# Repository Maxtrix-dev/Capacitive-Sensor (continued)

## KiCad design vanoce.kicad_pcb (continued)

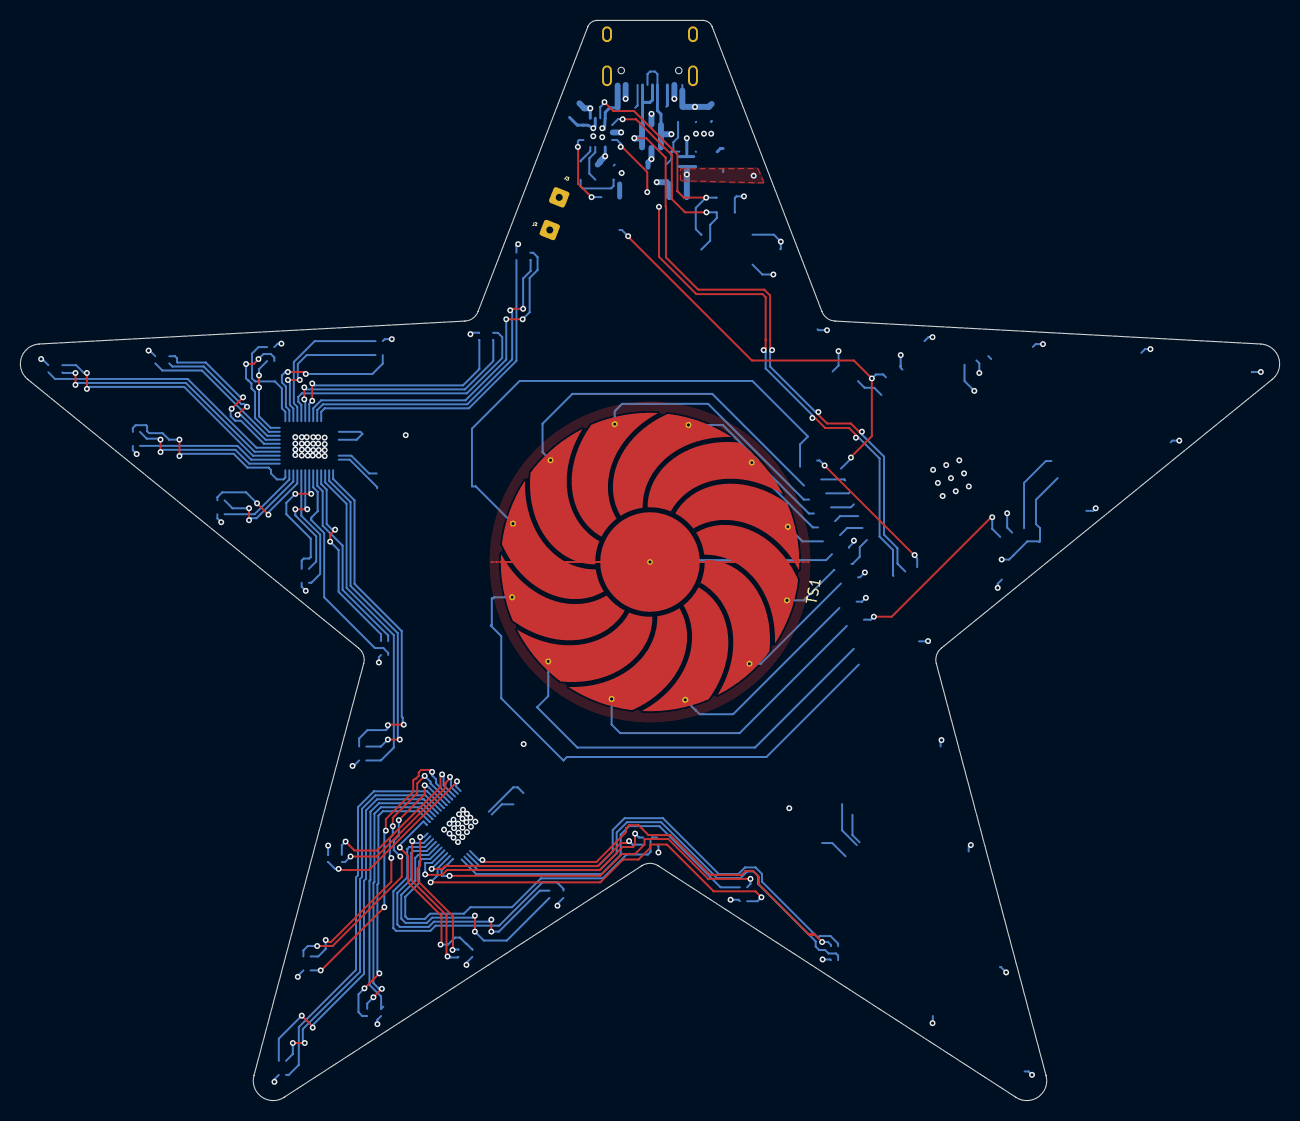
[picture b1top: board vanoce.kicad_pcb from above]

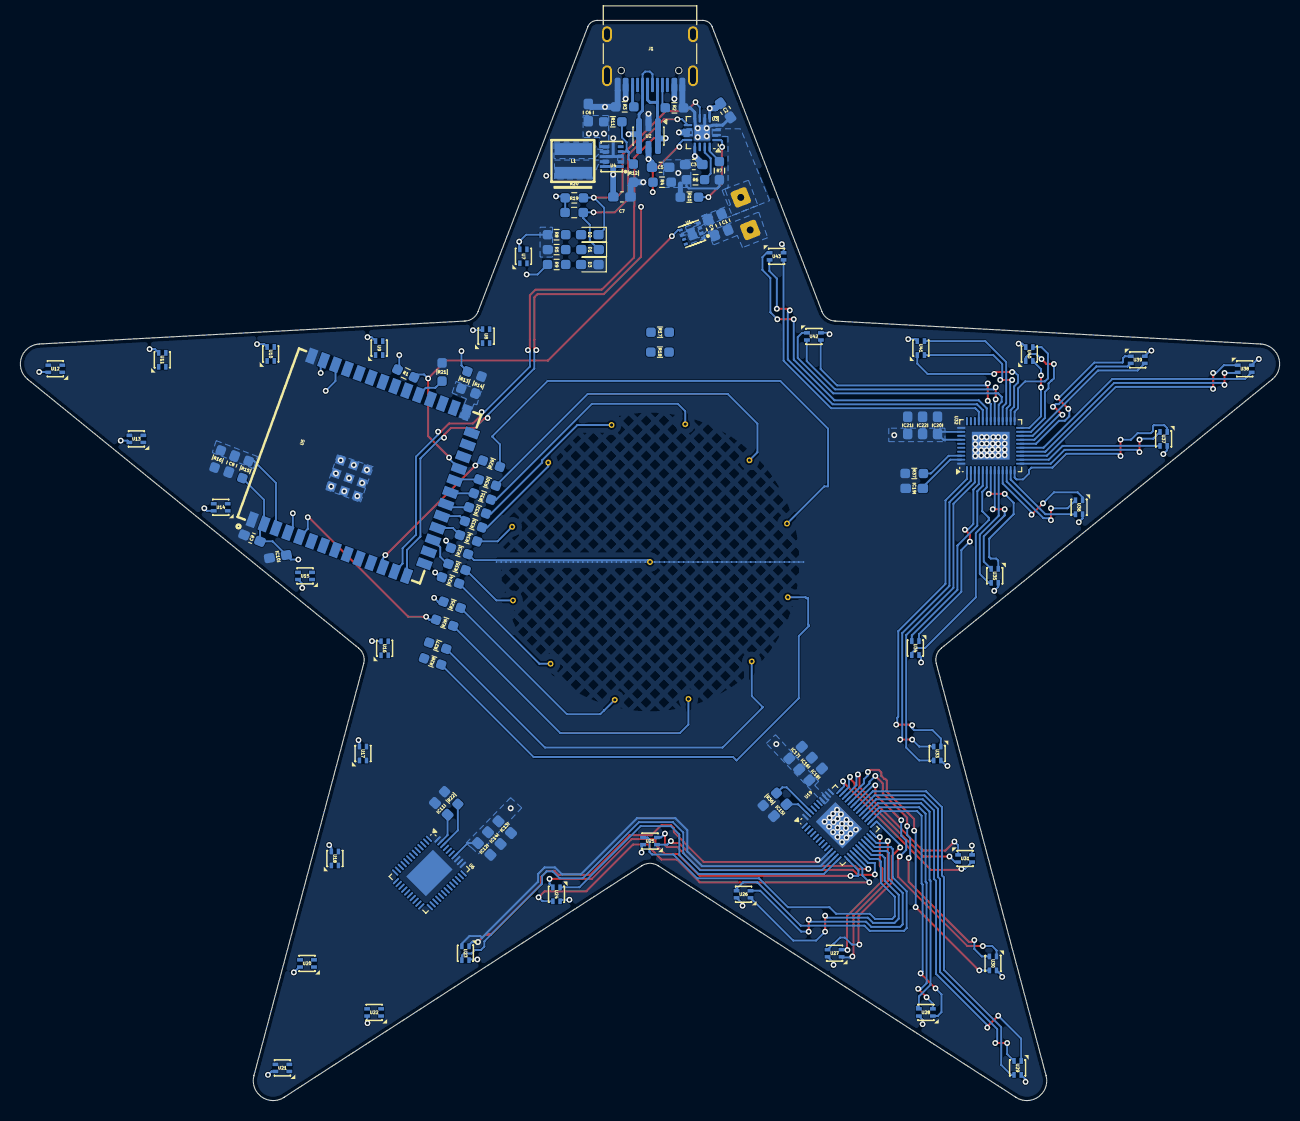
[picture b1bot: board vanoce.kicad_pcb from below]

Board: 4 copper layers, 126.6 x 108.6 mm, 110 parts (107 on the bottom side), 164 nets.

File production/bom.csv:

Designator,Footprint,Quantity,Value,LCSC Part #
"C1, C2",0603,2,4u7,
"C10_2, C10, C13, C17, C21, C5",0603,6,100n,
"C11, C12, C15, C16, C19, C20, C3, C8",0603,8,1u,
"C14, C18, C22, C7",0603,4,10u,
C4,0603,1,0.1u,
"C6, C9",0603,2,22u,
D1,0603,1,GREEN,
D2,0603,1,ORANGE,
D3,0603,1,BLUE,
J1,USB_C_Receptacle_HRO_TYPE-C-31-M-12,1,USB_C_Receptacle_USB2.0_16P,
"J2, J3",SolderWire-0.15sqmm_1x01_D0.5mm_OD1.5mm,2,Conn_01x01_Pin,
L1,IND-SMD_L4.0-W4.0_XFL4020-102MEB,1,XFL4015-471MEC,C18221164
"R1, R19, R20, R21",0603,4,100k,
"R10, R13, R15",0603,3,10k,
R11,0603,1,510k,
R12,0603,1,91k,
"R14, R16",0603,2,DNP,
"R17, R18",0603,2,4k7,
"R2, R3",0603,2,5k1,
"R22, R36, R37",0603,3,6k2,
"R23, R24, R25, R26, R27, R28, R29, R30, R31, R32, R33, R34, R35",0603,13,510R,
R4,0603,1,1k1,
R5,0603,1,6k,
R6,0603,1,4k1,
R7,0603,1,1k7,
R8,0603,1,750,
R9,0603,1,110,
U1,TDFN-8_L2.0-W2.0-P0.50-BL-EP1.2,1,MAX17048G+T10,C2682616
"U10, U11, U12, U13, U14, U15, U16, U17, U18, U20, U21, U22, U23, U24, U25, U26, U27, U28, U29, U30, U31, U33, U34, U35, U36, U37, U38, U39, U40, U41, U42, U43, U44, U7, U8, U9",LED-SMD_4P-L1.6-W1.5_WHITE-LED,36,XL-B1515RGBA-HF,C22461781
"U19, U32, U6",VQFN-46-1EP_5x6mm_P0.4mm_EP2.8x3.8mm,3,LP5036,
U2,SOT-23-6,1,WE-TVS-82400102,
U3,VQFN-16-1EP_3x3mm_P0.5mm_EP1.6x1.6mm,1,BQ24074RGT,
U4,VSON-10_L3.0-W2.0-P0.50-TL,1,TPS63802DLAR,C2845237
U5,WIRELM-SMD_ESP32-S3-WROOM-1U,1,ESP32-S3-WROOM-1U-N16,C2980298
